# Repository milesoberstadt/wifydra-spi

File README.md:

# Wifydra-SPI 

A distributed WiFi beacon sniffing system using an ESP32-S3-DevKitC-1 as a central Controller and multiple ESP32-C5 nodes as Workers, with one C5 node per WiFi channel. The device uses SPI to enable synchronization of time, GPS coordinates, and aggregate WiFi discovery data.

Shout out to [lozaning's Wifydra](https://github.com/lozaning/The_Wifydra) for the inspiration!

## Features
- **Passive:** Workers operate in promiscuous mode on a fixed channel, ensuring no missed beacons due to the channel hopping in an active scan.
- **Simplified flashing:** I used SPI's CS pin assignment as unique identifiers, channels are assigned at runtime by the controller. 
- **Wigle Compatibility:** Data is stored in Wigle-compatible structures with first-seen timestamps and RSSI tracking.

## Parts List
- **Controller:** ESP32-S3-DevKitC-1, chosen for its high GPIO count and native USB/SPI support
- **Workers:** 16x Seeed Studio ESP32-C5 (or other compatible ESP32 modules)
- **GPS:** NEO-6M u-blox module, any 5v module should work
- **SD Card:** I used a Pzsmocn microSD module, any 3.3v SPI module should work
- **Buck Converter:** Bucking from 5v to 3.3v for the SD card
- **Resistors:** Every SPI connected device (including the microSD) needs a 10k ohm resistor tying the device's 3.3v line to CS

## Hardware Wiring

Current prototype diagram: https://app.cirkitdesigner.com/project/823f8a95-0d39-48f3-8a6c-8a6a2daa64cd

### SPI Bus Connections
| Signal | ESP32-S3-DevKitC-1 (Controller) | ESP32-S3 (Worker x) | SD Card (SPI Mode) |
| :--- | :--- | :--- | :--- |
| **SCLK** | GPIO 12 | GPIO 7 | SCLK |
| **MISO** | GPIO 13 | GPIO 8 | MISO |
| **MOSI** | GPIO 11 | GPIO 9 | MOSI |
| **GND** | GND | GND | GND |

### Chip Select (CS) Connections
| Target | ESP32-S3-DevKitC-1 (Controller CS Pin) | ESP32-S3 (Worker CS Pin) |
| :--- | :--- | :--- |
| **Worker 1** | GPIO 4 | GPIO 2 |
| **Worker 2** | GPIO 5 | GPIO 2 |
| **Worker 3** | GPIO 6 | GPIO 2 |
| **Worker 4** | GPIO 7 | GPIO 2 |
| **Worker 5** | GPIO 15 | GPIO 2 |
| **Worker 6** | GPIO 18 | GPIO 2 |
| **Worker 7** | GPIO 8 | GPIO 2 |
| **Worker 8** | GPIO 9 | GPIO 2 |
| **Worker 9** | GPIO 2 | GPIO 2 |
| **Worker 10** | GPIO 42 | GPIO 2 |
| **Worker 11** | GPIO 41 | GPIO 2 |
| **Worker 12** | GPIO 40 | GPIO 2 |
| **Worker 13** | GPIO 39 | GPIO 2 |
| **Worker 14** | GPIO 21 | GPIO 2 |
| **Worker 15** | GPIO 10 | GPIO 2 |
| **Worker 16** | GPIO 14 | GPIO 2 |
| **SD Card** | GPIO 1 | N/A |

### GPS Connections (Controller Only)
| Peripheral | Signal | ESP32-S3-DevKitC-1 (Controller) | Notes |
| :--- | :--- | :--- | :--- |
| **GPS (UART2)** | TX | GPIO 17 | Connect to GPS RX |
| **GPS (UART2)** | RX | GPIO 16 | Connect to GPS TX |

## Requirements
- ESP-IDF 5.x environment sourced: `. $IDF_PATH/export.sh`

## Flashing 
- **Controller:**
  ```bash
  cd controller
  idf.py build
  idf.py flash
  ```
- **Worker:**
  ```bash
  cd worker
  idf.py build
  idf.py flash
  ```

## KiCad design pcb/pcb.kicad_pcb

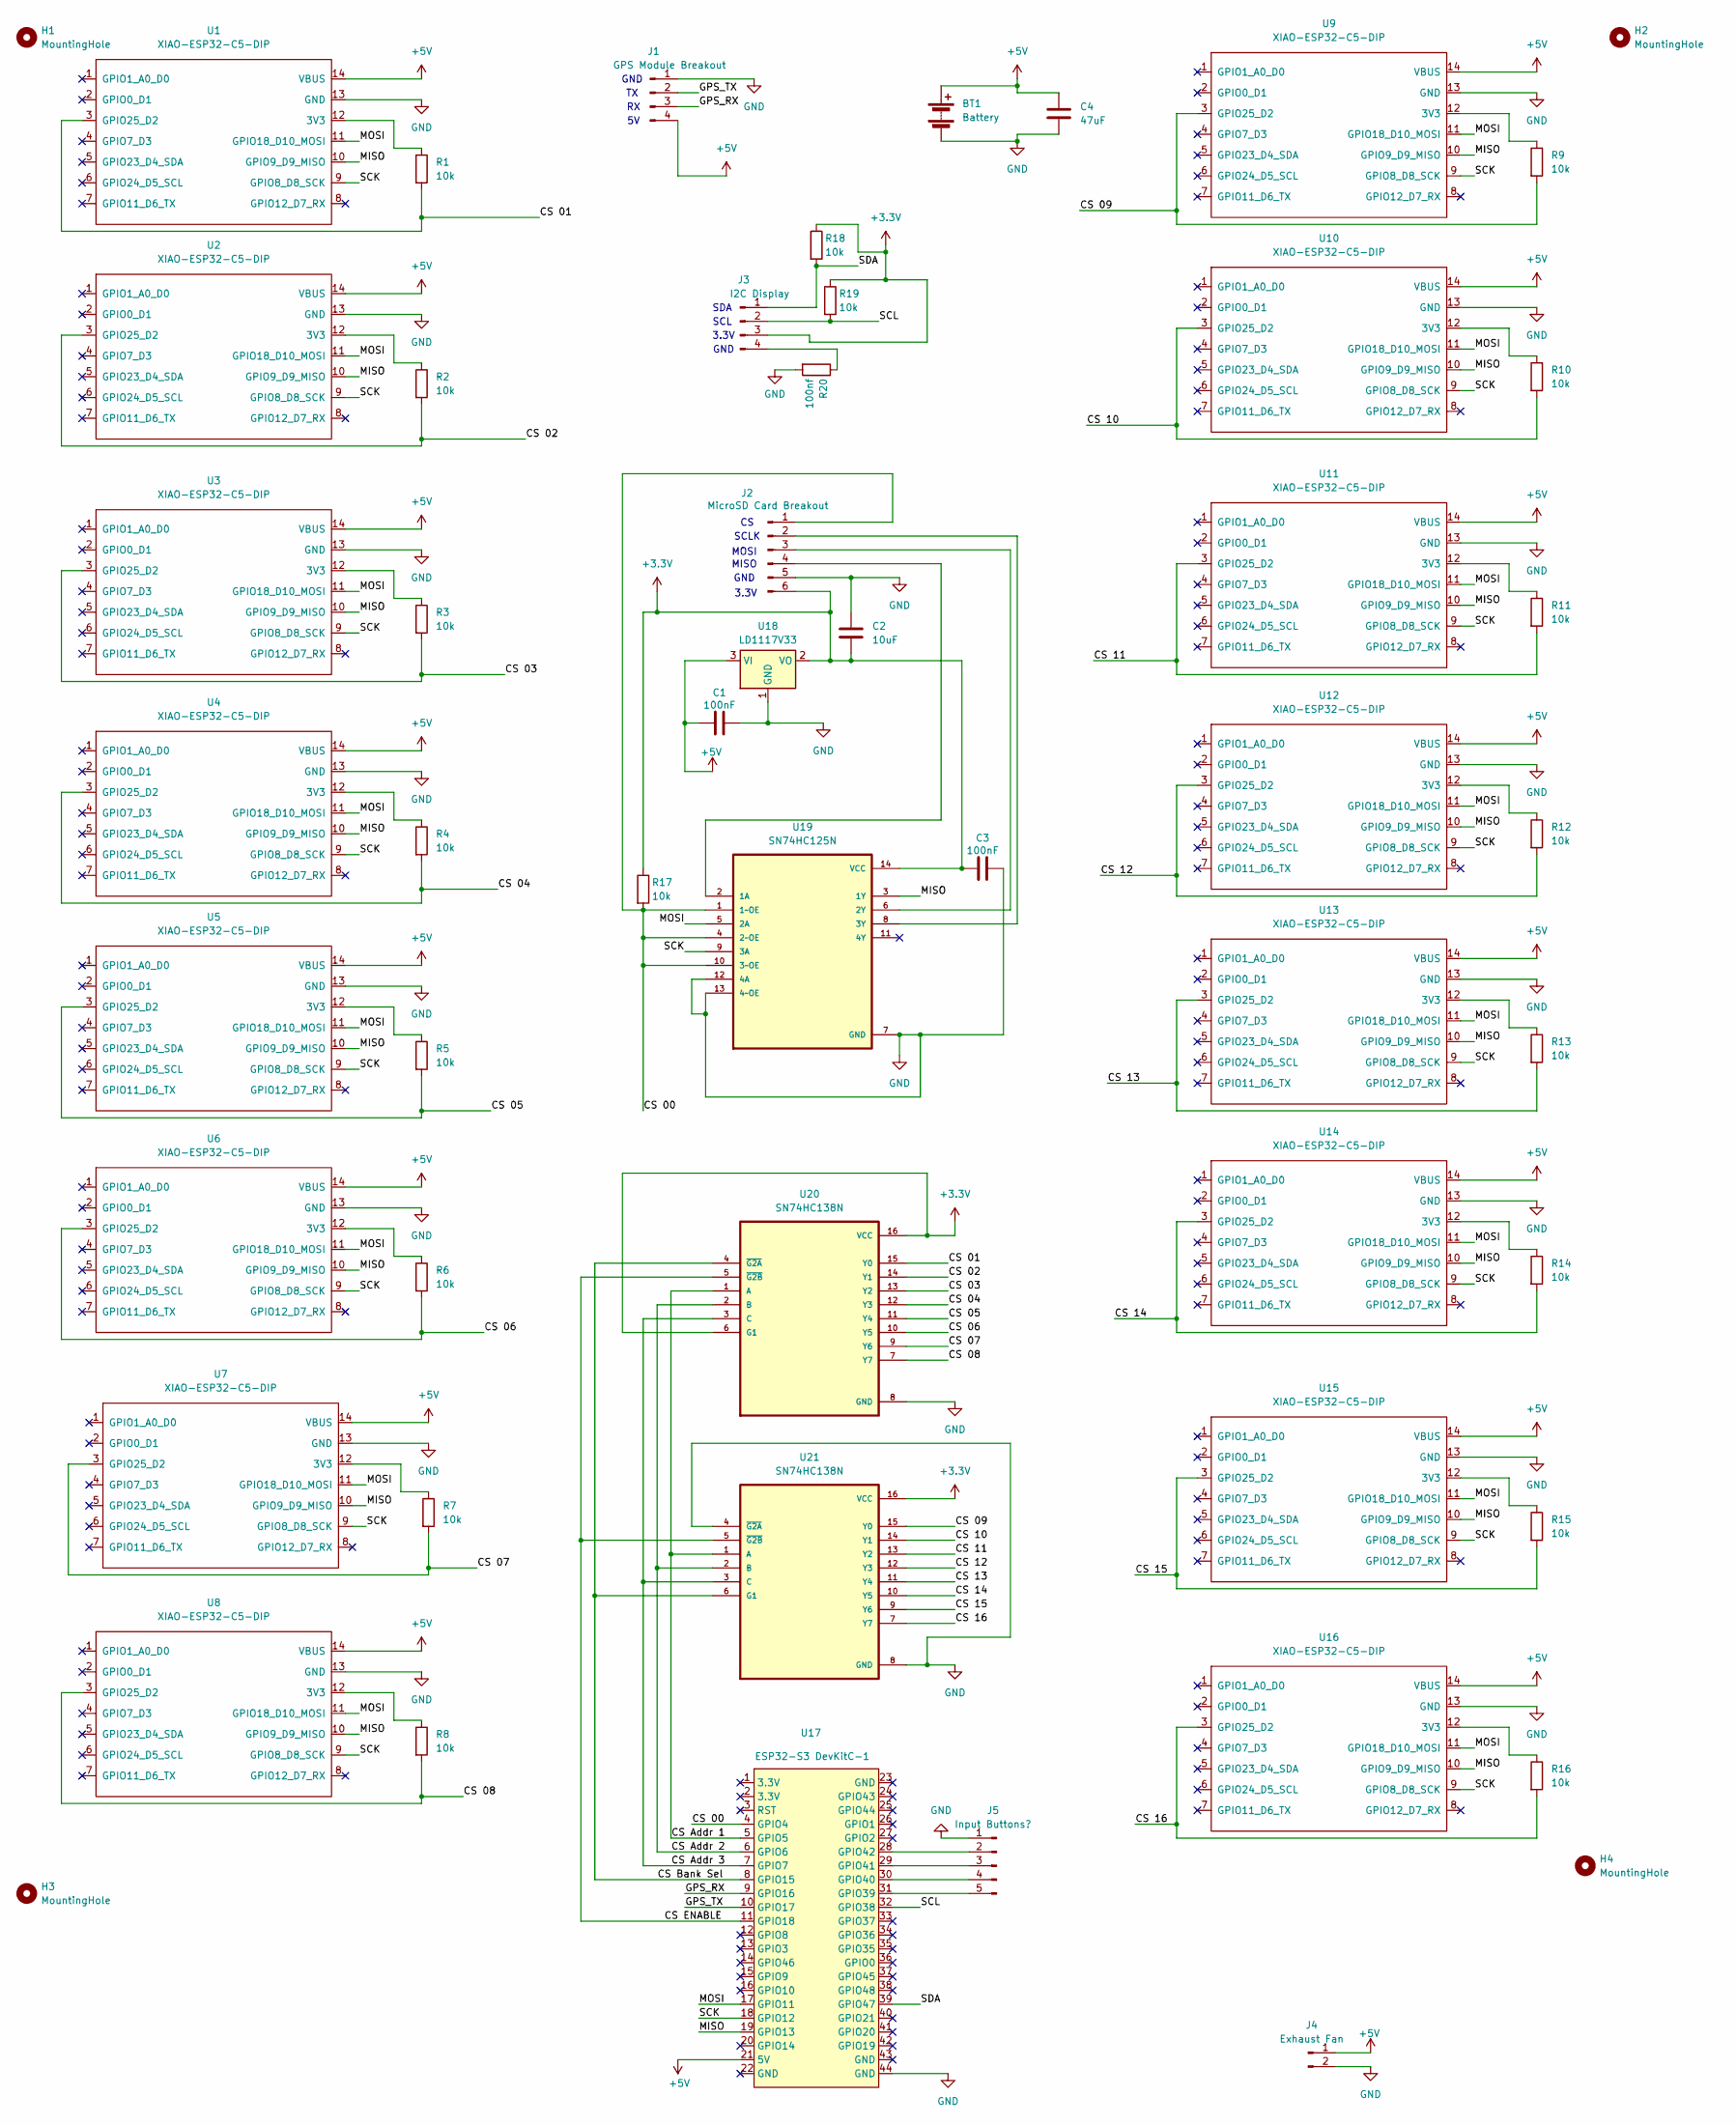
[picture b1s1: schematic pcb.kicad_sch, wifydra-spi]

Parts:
BT1: Battery; PinHeader_1x02_P2.54mm_Vertical
C1, C3: 100nF; C_Disc_D5.0mm_W2.5mm_P2.50mm
C2: 10uF; C_Disc_D5.0mm_W2.5mm_P2.50mm
C4: 47uF; C_Disc_D5.0mm_W2.5mm_P2.50mm
H1, H2, H3, H4: MountingHole; MountingHole_3.2mm_M3
J1: GPS Module Breakout; PinHeader_1x04_P2.54mm_Vertical
J2: MicroSD Card Breakout; PinHeader_1x06_P2.54mm_Vertical
J3: I2C Display; PinHeader_1x04_P2.54mm_Vertical
J4: Exhaust Fan; PinHeader_1x02_P2.54mm_Vertical
J5: Input Buttons?; PinHeader_1x04_P2.54mm_Vertical
R1, R2, R3, R4, R5, R6, R7, R8, R9, R10, R11, R12, R13, R14, R15, R16, R17, R18, R19: 10k; R_Axial_DIN0204_L3.6mm_D1.6mm_P5.08mm_Horizontal
R20: 100nf; R_Axial_DIN0204_L3.6mm_D1.6mm_P5.08mm_Horizontal
U1, U2, U3, U4, U5, U6, U7, U8, U9, U10, U11, U12, U13, U14, U15, U16: XIAO-ESP32-C5-DIP
U17: ESP32-S3 DevKitC-1; ESP32-S3-DevKitC
U18: LD1117V33; TO-220-3_Vertical
U19: SN74HC125N; DIP-14_W7.62mm_LongPads
U20, U21: SN74HC138N; DIP794W45P254L1969H508Q16; DigiKey_Part_Number 296-1575-5-ND

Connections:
+3.3V: C2.1, C3.2, J2.6, J3.3, R17.1, R18.1, R19.1, U18.2 (VO), U19.14 (VCC), U20.6 (G1), U20.16 (VCC), U21.16 (VCC)
+5V: BT1.1 (+), C1.2, C4.2, J1.4, J4.1, U1.14 (VBUS), U2.14 (VBUS), U3.14 (VBUS), U4.14 (VBUS), U5.14 (VBUS), U6.14 (VBUS), U7.14 (VBUS), U8.14 (VBUS), U9.14 (VBUS), U10.14 (VBUS), U11.14 (VBUS), U12.14 (VBUS), U13.14 (VBUS), U14.14 (VBUS), U15.14 (VBUS), U16.14 (VBUS), U17.21 (5V), U18.3 (VI)
/CS 00: J2.1, R17.2, U17.4 (GPIO4), U19.1 (1~OE), U19.4 (2~OE), U19.10 (3~OE)
/CS 01: R1.2, U1.3 (GPIO25_D2), U20.15 (Y0)
/CS 02: R2.2, U2.3 (GPIO25_D2), U20.14 (Y1)
/CS 03: R3.2, U3.3 (GPIO25_D2), U20.13 (Y2)
/CS 04: R4.2, U4.3 (GPIO25_D2), U20.12 (Y3)
/CS 05: R5.2, U5.3 (GPIO25_D2), U20.11 (Y4)
/CS 06: R6.2, U6.3 (GPIO25_D2), U20.10 (Y5)
/CS 07: R7.2, U7.3 (GPIO25_D2), U20.9 (Y6)
/CS 08: R8.2, U8.3 (GPIO25_D2), U20.7 (Y7)
/CS 09: R9.2, U9.3 (GPIO25_D2), U21.15 (Y0)
/CS 10: R10.2, U10.3 (GPIO25_D2), U21.14 (Y1)
/CS 11: R11.2, U11.3 (GPIO25_D2), U21.13 (Y2)
/CS 12: R12.2, U12.3 (GPIO25_D2), U21.12 (Y3)
/CS 13: R13.2, U13.3 (GPIO25_D2), U21.11 (Y4)
/CS 14: R14.2, U14.3 (GPIO25_D2), U21.10 (Y5)
/CS 15: R15.2, U15.3 (GPIO25_D2), U21.9 (Y6)
/CS 16: R16.2, U16.3 (GPIO25_D2), U21.7 (Y7)
/CS Addr 1: U17.5 (GPIO5), U20.1 (A), U21.1 (A)
/CS Addr 2: U17.6 (GPIO6), U20.2 (B), U21.2 (B)
/CS Addr 3: U17.7 (GPIO7), U20.3 (C), U21.3 (C)
/CS Bank Sel: U17.8 (GPIO15), U20.4 (~G2A), U21.6 (G1)
/CS ENABLE: U17.11 (GPIO18), U20.5 (~G2B), U21.5 (~G2B)
/GPS_RX: J1.3, U17.9 (GPIO16)
/GPS_TX: J1.2, U17.10 (GPIO17)
/MISO: U1.10 (GPIO9_D9_MISO), U2.10 (GPIO9_D9_MISO), U3.10 (GPIO9_D9_MISO), U4.10 (GPIO9_D9_MISO), U5.10 (GPIO9_D9_MISO), U6.10 (GPIO9_D9_MISO), U7.10 (GPIO9_D9_MISO), U8.10 (GPIO9_D9_MISO), U9.10 (GPIO9_D9_MISO), U10.10 (GPIO9_D9_MISO), U11.10 (GPIO9_D9_MISO), U12.10 (GPIO9_D9_MISO), U13.10 (GPIO9_D9_MISO), U14.10 (GPIO9_D9_MISO), U15.10 (GPIO9_D9_MISO), U16.10 (GPIO9_D9_MISO), U17.19 (GPIO13), U19.3 (1Y)
/MOSI: U1.11 (GPIO18_D10_MOSI), U2.11 (GPIO18_D10_MOSI), U3.11 (GPIO18_D10_MOSI), U4.11 (GPIO18_D10_MOSI), U5.11 (GPIO18_D10_MOSI), U6.11 (GPIO18_D10_MOSI), U7.11 (GPIO18_D10_MOSI), U8.11 (GPIO18_D10_MOSI), U9.11 (GPIO18_D10_MOSI), U10.11 (GPIO18_D10_MOSI), U11.11 (GPIO18_D10_MOSI), U12.11 (GPIO18_D10_MOSI), U13.11 (GPIO18_D10_MOSI), U14.11 (GPIO18_D10_MOSI), U15.11 (GPIO18_D10_MOSI), U16.11 (GPIO18_D10_MOSI), U17.17 (GPIO11), U19.5 (2A)
/SCK: U1.9 (GPIO8_D8_SCK), U2.9 (GPIO8_D8_SCK), U3.9 (GPIO8_D8_SCK), U4.9 (GPIO8_D8_SCK), U5.9 (GPIO8_D8_SCK), U6.9 (GPIO8_D8_SCK), U7.9 (GPIO8_D8_SCK), U8.9 (GPIO8_D8_SCK), U9.9 (GPIO8_D8_SCK), U10.9 (GPIO8_D8_SCK), U11.9 (GPIO8_D8_SCK), U12.9 (GPIO8_D8_SCK), U13.9 (GPIO8_D8_SCK), U14.9 (GPIO8_D8_SCK), U15.9 (GPIO8_D8_SCK), U16.9 (GPIO8_D8_SCK), U17.18 (GPIO12), U19.9 (3A)
/SCL: J3.2, R19.2, U17.32 (GPIO38)
/SDA: J3.1, R18.2, U17.39 (GPIO47)
GND: BT1.2 (-), C1.1, C2.2, C3.1, C4.1, J1.1, J2.5, J4.2, J5.1, R20.2, U1.13 (GND), U2.13 (GND), U3.13 (GND), U4.13 (GND), U5.13 (GND), U6.13 (GND), U7.13 (GND), U8.13 (GND), U9.13 (GND), U10.13 (GND), U11.13 (GND), U12.13 (GND), U13.13 (GND), U14.13 (GND), U15.13 (GND), U16.13 (GND), U17.44 (GND), U18.1 (GND), U19.7 (GND), U19.12 (4A), U19.13 (4~OE), U20.8 (GND), U21.4 (~G2A), U21.8 (GND)
unnamed: J2.2, U19.8 (3Y)
unnamed: J2.3, U19.6 (2Y)
unnamed: J2.4, U19.2 (1A)
unnamed: J3.4, R20.1
unnamed: J5.2, U17.28 (GPIO42)
unnamed: J5.3, U17.29 (GPIO41)
unnamed: J5.4, U17.30 (GPIO40)
unnamed: J5.5, U17.31 (GPIO39)
unnamed: R1.1, U1.12 (3V3)
unnamed: R2.1, U2.12 (3V3)
unnamed: R3.1, U3.12 (3V3)
unnamed: R4.1, U4.12 (3V3)
unnamed: R5.1, U5.12 (3V3)
unnamed: R6.1, U6.12 (3V3)
unnamed: R7.1, U7.12 (3V3)
unnamed: R8.1, U8.12 (3V3)
unnamed: R9.1, U9.12 (3V3)
unnamed: R10.1, U10.12 (3V3)
unnamed: R11.1, U11.12 (3V3)
unnamed: R12.1, U12.12 (3V3)
unnamed: R13.1, U13.12 (3V3)
unnamed: R14.1, U14.12 (3V3)
unnamed: R15.1, U15.12 (3V3)
unnamed: R16.1, U16.12 (3V3)

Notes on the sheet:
3.3V
SCL
GND
MISO
SDA
MOSI
SCLK

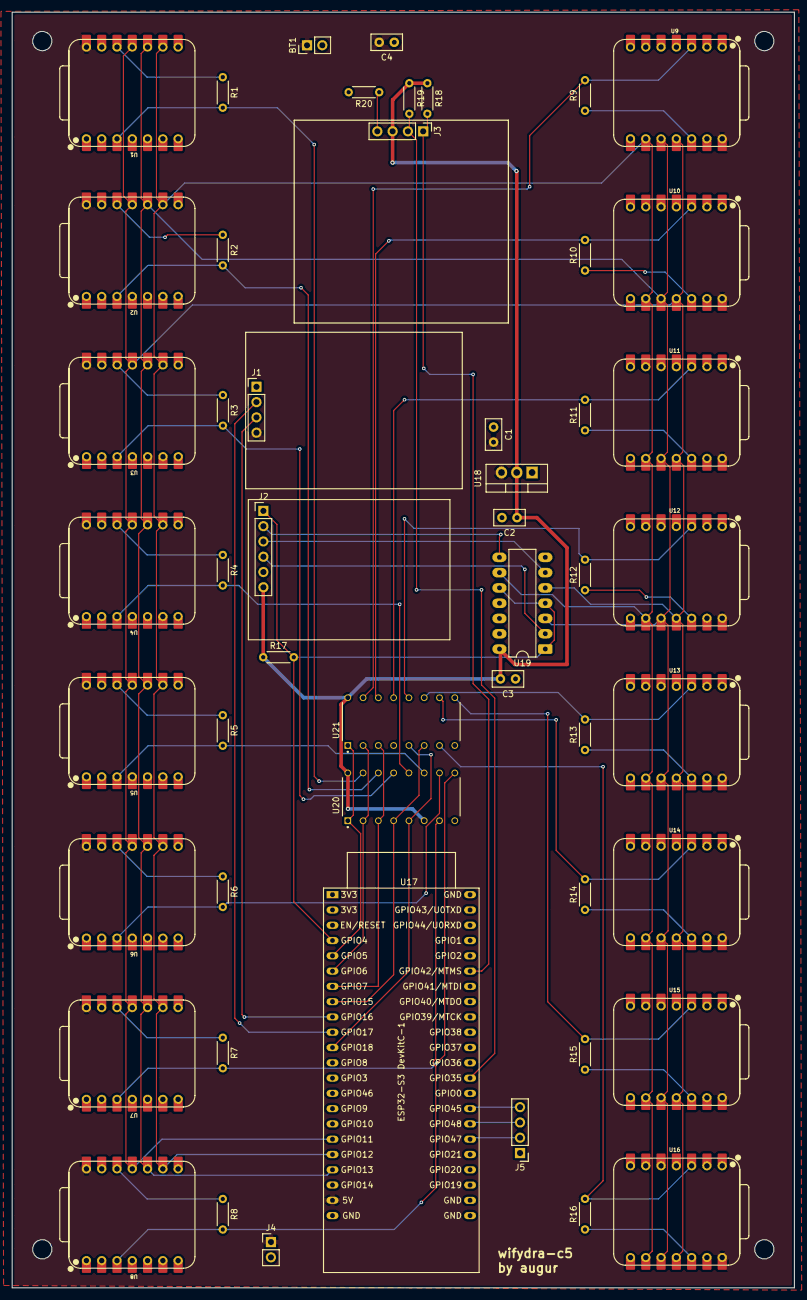
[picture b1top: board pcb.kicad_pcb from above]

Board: 2 copper layers, 130.0 x 212.0 mm, 55 parts (0 on the bottom side), 55 nets.

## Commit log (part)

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2026-03-04 Initial commit, working output
2026-03-04 default to 1MHz
2026-03-04 change message struct to assign a wifi channel and send current GPS
2026-03-04 Add ap scanning, controller should now receive first two found APs
2026-03-04 decouple from command syntax, wait for workers to scan until they are assigned a channel
2026-03-04 track sent status of records
2026-03-05 overwrite old records if worker finds >500 aps
2026-03-05 get organized
2026-03-05 update PLAN.md with our future work
2026-03-05 Add gps module support
2026-03-08 Fix a bug and add blink for GPS lock status
2026-03-08 use ubx commands to seed gps for faster first fix
2026-03-08 wait to scan until we have gps fix
2026-03-08 add shopping list because that's what I'm blocked on now
2026-03-13 add microsd fs support
2026-03-28 Replace sdmmc interface with sd spi module, we're writing headers correctly!
2026-03-28 Add long filename support and create files on the sd card with the timestamp from GPS
2026-03-28 Writing APs to SD card correctly!!!
2026-04-04 bsides sd firmware
2026-05-09 tidy up
2026-05-09 rm old reference
2026-05-09 init a kicad 10 project
2026-05-09 Start the schematic for the PCB
2026-06-20 More wiring on the PCB design
2026-06-21 tidy schematic
2026-06-22 Increase worker count to 16, wire up the PCB
2026-06-22 tidy up warnings
2026-06-22 more progress with the PCB layout
2026-06-22 swap voltage regulator for an LD1117v33 regulator
2026-06-22 more tweaks before routing
